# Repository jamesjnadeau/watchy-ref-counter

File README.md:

Intial prompt:

Based on the firmware available here: 

https://github.com/sqfmi/Watchy

I have clone the repo locally at ../Watchy

I'm creating a purpose built countdown timer used for reffing a football game. 

The user should see a countdown on the screen that updates every second. 
The count down should have 2 configurable start timers, start with 40 and 25 as defaults.
The user should use the two buttons on the right hand side of the device to start the timers. The top one should be the longer value
The timer buttons should have a configurable hold down before it acts as a reset of the timer, or to start the timer in general. Make it be 0.5 seconds as a default.

When the timer is up, it should buzz a configurable time, start with 1 second. 
Before the timer reaches a configurable number of seconds, default with 10 seconds, it should buzz a configurable number of times, start with 1. By default it should buzz once at 10 seconds. 

It should count down the last 5 seconds by buzzing at each second mark. So it should buzz at 5, 4, 3, 2, and 1, then do the finall configuable buzz time.
The top left button, after being held down for a configurable ammount of time, different than the above one, default 1 second, should then put the device into low power mode. The device should wake back up to normal operating mode if this button is pressed again, If in lower power mode, it should say sleeping on the display.

Please create a read me seciton below the line that documents the structure of the repo and how to install it on the device.

---

# Watchy Ref Counter

A countdown timer for sports officials, running on a
[Watchy](https://watchy.sqfmi.com) e-paper watch. Seven presets — football,
lacrosse, NCAA and NFHS baseball, NCAA and NFHS softball, and a custom slot —
each with two countdowns, big 7-segment digits, and a buzz pattern you can
follow without looking at your wrist.

**This repo stands alone.** It does not link against the
[Watchy library](https://github.com/sqfmi/Watchy); the panel is driven through
GxEPD2, the RTC chips directly over I2C, NTP through the ESP32 core's own SNTP
client, and the Bluetooth time sync through its BLE stack. Where the behaviour follows that firmware — the menu, the
set-time screen, the pin map — the comments credit it, but none of its code is
here. It builds with the reference repo nowhere on disk.

## Controls

Watchy's four buttons, by physical position:

```
   BACK (top left)  ----+---------+---- UP   (top right)
                        |  200 x  |
   MENU (bottom left) --|  200    |---- DOWN (bottom right)
                        +---------+
```

Watch out for the names: on Watchy, **MENU is the bottom-left button and BACK
is the top-left one**, which is the opposite of what they sound like.

| Button | Action | Default hold |
| --- | --- | --- |
| Top right | Start, or reset, the active preset's **long** clock | 0.5s |
| Bottom right | Start, or reset, the active preset's **short** clock | 0.5s |
| Top left | Enter low power mode; hold again to wake | 1.0s |
| Bottom left | On Ready, open the settings menu; otherwise clear the clock | 0.5s |

The two right-hand buttons always run whichever preset is active — see
*Sports* below — rather than a fixed 40 and 25 seconds.

The bottom-left button does two jobs because on the Ready screen there is no
clock to clear. Hold it there and you get the reference Watchy menu; hold it
while a clock is up and it clears back to Ready.

**A short tap does nothing.** Every action needs a deliberate hold, so a button
brushed against a sleeve mid-game cannot reset the play clock. A short
confirmation buzz fires the instant a hold registers, so you know the clock
started without looking down.

Holding a timer button while that clock is already running restarts it from
its full value.

## Sports

The right-hand buttons run whichever preset is active. Seven ship in the box
— six fixed sports plus one editable Custom slot:

| Name | Description |
| --- | --- |
| Football | football |
| Lacrosse | lacrosse shot |
| Base NCAA | NCAA baseball |
| Base NFHS | NFHS baseball |
| Soft NCAA | NCAA softball |
| Soft NFHS | NFHS softball |
| Custom | user set |

Their clock lengths and buzz marks are in *Buzz pattern*, below. `Football`
reproduces exactly what this firmware shipped with before presets existed, so
a watch that has never opened the menu behaves the same as it always did.

The active choice comes from the menu's `Sport` row, which opens a scrolling
picker: UP/DOWN moves, MENU selects and persists, BACK leaves the stored
choice alone. Like the time zone, it is kept in NVS, so it survives a
reflash — the sport a watch is set to is a property of who is carrying it,
not of the firmware on it.

Each row shows a preset's name and its two clock values; the footer below
shows the highlighted preset's description, its position in the list, and its
two warning marks as `warn <first>/<second>`. The final-countdown value isn't
there — it's 5 for every fixed preset, so it never tells two of them apart,
and it's shown spelled out on the Custom editor instead, the one preset that
can change it.

The six fixed presets are read-only. `Edit Custom` opens the one preset that
can be changed: five fields — Long, Short, Warn 1, Warn 2, Final — with
MENU stepping to the next field and committing once past the last one, BACK
stepping back, and UP/DOWN changing the value under the cursor, the same
interaction Set Time uses. The two clocks clamp to 1–199 seconds; the three
marks clamp to 0–199, where 0 turns that mark off. Editing Custom does not
select it — pick `Custom` from the `Sport` screen to make it active, the same
separation the zone picker keeps between "known" and "in use".

## Buzz pattern

Every preset buzzes on the same four events, at the marks that preset sets:

| Event | Buzz |
| --- | --- |
| First warning, at `warnAtSeconds` remaining | `WARNING_BUZZ_COUNT` (1) short buzz |
| Second warning, at `warn2AtSeconds` remaining | `WARNING_BUZZ_COUNT_2` (2) short buzzes |
| Final countdown, at or below `finalCountdownFrom` | 1 short buzz (150ms) on each second mark |
| Expire, at 0 | 1 long buzz (1000ms) |

A mark of 0 turns it off — Football's second warning ships off, which is why
the stock clock only ever buzzes once early. A mark that falls at or inside
the final countdown is silently swallowed by the per-second buzz, which
already covers it. The two buzz counts and the expire length are global, in
`settings.h`; the marks themselves are per-preset, in `RefSport.cpp`:

| Name | Long | Short | Warn 1 | Warn 2 | Final from |
| --- | --- | --- | --- | --- | --- |
| Football | 40 | 25 | 10 | – | 5 |
| Lacrosse | 120 | 20 | 30 | 10 | 5 |
| Base NCAA | 120 | 20 | 30 | 10 | 5 |
| Base NFHS | 80 | 20 | 30 | 10 | 5 |
| Soft NCAA | 90 | 20 | 30 | 10 | 5 |
| Soft NFHS | 60 | 20 | 20 | 10 | 5 |
| Custom | 40 | 25 | 10 | – | 5 |

Every mark above is in seconds **remaining**, matching what the clock counts
down. This is worth being deliberate about, because
[ReadyRef](https://ready-ref.com/personal-timers/) — the commercial timers
this preset table is modelled on — quote their pre-warnings in seconds
*elapsed*. Their football timer's "30 second pre-warning" on a 40 second
clock is the same moment as Football's `Warn 1` of 10 above: 30 seconds in is
10 seconds left. Getting that backwards would fire the warning at the wrong
end of the play.

Buzzes are deliberately blocking, and fire *before* the screen redraws: the
buzz is the cue you actually react to, and an e-paper refresh takes most of a
second. This costs no accuracy, because remaining time is always recomputed
from the timestamp the clock started at rather than accumulated tick by tick.

## Screens

Every screen carries the wall clock at the top left and a battery gauge at the
top right.

**Ready** — shown at boot and on wake. Both of the active preset's clocks
stacked to line up with the two right-hand buttons that start them. The
footer shows the active sport's name, in capitals, in place of `HOLD TO
START` — the thing worth checking before kickoff is which preset is loaded,
not how the buttons work.

**Running** — the current clock, large, updating every second. The header is
the same wall clock and battery gauge every screen carries; it does not say
which of the two clocks is counting.

**Time expired** — `00` holds for `EXPIRED_HOLD_MS` (3s), long enough to
register the delay of game, then the watch drops back to Ready on its own.
Starting a new clock during that window cancels the return.

**Sleeping** — low power mode.

**Menu** — held open from Ready. Navigation follows the reference: UP/DOWN to
move, MENU (bottom left) to select, BACK (top left) to leave. It also drops
back to Ready by itself after `MENU_TIMEOUT_MS`, so a menu opened by accident
cannot strand you mid-game. Nine entries do not fit the panel at once, so the
list scrolls a seven-row window, keeping the highlighted entry in view the same
way the time zone picker already does. Two of the nine are conditional — **Sync
NTP** and **Sync BT** — and with neither on offer the remaining seven fit
without scrolling at all.

Every screen the menu opens times out on the same rule, and a timeout always
**discards**: Set Time leaves the clock alone, Edit Custom leaves the stored
preset alone, and the two pickers leave their stored choice alone. Only
pressing MENU past the last field commits. This matters more than it sounds —
these screens repaint about twice a second, so one left open would otherwise
hold the panel refreshing until the battery went flat.

| Entry | What it does |
| --- | --- |
| About | Version, board name, battery, time, uptime, last sync, RTC type |
| Sync NTP | Connect and set the clock from `NTP_SERVER`. Only listed once **Setup WiFi** has connected |
| Sync BT | Set the clock from a phone over Bluetooth. Listed whenever `BT_TIME_SYNC` is on |
| TZ: *name* | Pick a US time zone from a scrolling list |
| DST: Auto/Off | Turn the daylight saving rule on or off |
| Set Time | Set the clock by hand, no WiFi needed |
| Setup WiFi | Captive portal to save credentials |
| Sport: *name* | Pick one of the seven presets from a scrolling list |
| Edit Custom | Set the five Custom fields by hand |

The **Sport**, **TZ** and **DST** rows show their current value rather than
fixed text, so the menu doubles as the status display for all three. **DST**
toggles in place and redraws with a fast partial refresh; everything else
opens a screen.

**Sync NTP** is hidden until **Setup WiFi** has connected successfully, since
with no credentials stored it could only ever report a failure. The watch
remembers that in NVS (`RefWifi.cpp`), so it survives a reflash — but a watch
upgraded from a firmware without that flag has nothing stored and will hide the
row until **Setup WiFi** is run once more. A setup that fails or times out
clears the flag again, correctly: that screen wipes the saved credentials
before it raises its access point.

**Sync BT** is the other way round: it needs nothing saved, so it is there from
the first boot. It advertises the watch for `BT_SYNC_TIMEOUT_MS` (60s) and
waits for a phone to write the time; the screen says when a phone has
connected, BACK gives up early, and the result screen names the zone the
conversion used. See *Setting the clock from a phone* below for what to press
on the phone.

There is no "Show Accelerometer". The reference has one, but nothing on a play
clock reads the sensor, and leaving it out means the BMA423 is never powered
up at all. There is no "Vibrate Motor" buzz test either — the buzzer announces
every warning mark and every expiry, so a dedicated screen for it earned a menu
row it did not need.

## Time zones and daylight saving

The RTC holds UTC. The zone offset is applied on the way out, every time the
clock is read, which is what makes the two menu entries cheap: changing zone or
flipping the DST switch takes effect on the next redraw and never rewrites the
clock chip.

The **TZ** entry lists all eleven US zones by name, with their standard offset
on the row and the abbreviations and region underneath:

| Zone | Standard | Daylight | Where |
| --- | --- | --- | --- |
| Eastern | UTC−5 EST | EDT | NY, DC, Atlanta, Miami |
| Central | UTC−6 CST | CDT | Chicago, Dallas, Minneapolis |
| Mountain | UTC−7 MST | MDT | Denver, Salt Lake, Albuquerque |
| Arizona | UTC−7 MST | — | most of Arizona |
| Pacific | UTC−8 PST | PDT | LA, Seattle, SF, Las Vegas |
| Alaska | UTC−9 AKST | AKDT | most of Alaska |
| Aleutian | UTC−10 HST | HDT | western Aleutians |
| Hawaii | UTC−10 HST | — | Hawaii |
| Samoa | UTC−11 SST | — | American Samoa |
| Atlantic | UTC−4 AST | — | Puerto Rico, USVI |
| Chamorro | UTC+10 ChST | — | Guam, N. Marianas |

**DST: Auto** means the US federal rule is applied when the date calls for it —
forward at 02:00 local standard on the second Sunday in March, back at 02:00
local daylight on the first Sunday in November — not that the clock is shifted
year round. Nothing needs doing at a changeover: the offset is computed from
the instant being displayed, so the watch is right on both sides of it and
right again if it is rebooted or asleep across it. **DST: Off** pins the zone
to standard time all year. The five zones with no daylight saving ignore the
switch either way.

Both settings are stored in NVS, so they survive a reflash — the zone is a
property of where the watch is, not of the firmware on it. `DEFAULT_TIME_ZONE`
and `DEFAULT_DST_AUTO` in `settings.h` are only the starting point, used until
the menu has been used once.

The rule is the one in force since 2007 (Energy Policy Act of 2005). It is
verified against the real transition dates for 2024–2027 and 2030 in every
zone; see *Testing* below. Set Time is exact except for the one hour a year
that springing forward deletes — typing 02:30 on that morning stores 01:30,
because 02:30 never happens.

## Timekeeping

The time comes from the watch's RTC chip, which `RefRtc` probes for at boot —
a PCF8563 at 0x51 on the V2.0, an RV-3028-C7 at 0x52 on the C6 board. It
keeps running through low power mode and
through a reflash, so the watch only needs setting once. The About screen
reports which one was found.

The chip is kept in UTC, not local time. That is what lets the zone and DST
settings change with no clock write and no drift, and it means an NTP sync
needs no offset applied to it.

Drift is handled three ways. **Set Time** sets it by hand, in local time.
**Sync BT** sets it from a phone over Bluetooth, with no WiFi involved.
**Sync NTP** sets it from the internet, on demand from the menu. It also runs
itself automatically once WiFi credentials have been saved, on a schedule
that needs both of these to be true: the watch has sat untouched — no button
press, no sleep entry — for `NTP_RESYNC_HOURS` (3 by default), and at least
`NTP_MIN_SYNC_INTERVAL_HOURS` (24) have passed since the last attempt, so a
run of idle moments in a row cannot trigger back-to-back radio activity.
Sleep entry counts as activity in its own right, so putting the watch away
resets the quiet clock rather than letting it tick through the night. Set
`NTP_RESYNC_HOURS` to 0 to only ever sync by hand. A PCF8563 drifts roughly a
minute a month, so even a daily sync keeps that under a second. The C6 board's
RV-3028-C7 is factory trimmed to about half a minute a year, and needs the
sync far less.

The two chips do not share a register layout, and the difference is the kind
that fails quietly: the PCF8563 holds the date at 0x05 and the weekday at
0x06, while the RV-3028 has the weekday at 0x03 and the date at 0x04. Decoding
one with the other's map yields a day of the month between 0 and 6 — wrong,
but shaped like a date. `tests/rtc_test.cpp` pins both layouts against a stub
I2C bus, which is the only part of this that can be checked without hardware.

An automatic sync blocks for several seconds while the radio comes up, which
is why it waits for quiet rather than firing the moment nobody is looking.
That holds even in low power mode: the watch arms a deep-sleep timer against
the same schedule, wakes itself when a sync falls due, syncs, and goes
straight back to sleep — the SLEEPING screen already on the panel is never
touched. It never runs while a clock is counting.

### Setting the clock from a phone

**Sync BT** is for the case WiFi does not cover: a field with no network you
have credentials for, and a phone in your pocket that knows the time.

The watch is the peripheral. While the screen is open it advertises the
standard Bluetooth **Current Time Service** (`0x1805`) under `BT_DEVICE_NAME`,
and the phone connects and *writes* the time into it. That direction is the
only one that works without an app written for this watch: neither iOS nor
Android will hand its clock to an arbitrary peripheral that asks for it, but
writing into a watch's Current Time Service is exactly what the service is
for. It is the same route the open source PineTime firmware takes, which is
why the apps that already do it work here unchanged:

| On the phone | What to do |
| --- | --- |
| **Gadgetbridge** (Android, F-Droid) | Pair the watch as a generic device; it syncs time to a connected device on its own |
| **nRF Connect** (Android / iOS) | Connect, open service `0x1805`, write characteristic `0x2A2B` |
| Anything else that syncs time to a BLE watch | Point it at the Current Time Service |

Two characteristics are accepted, both standard:

| UUID | What it carries |
| --- | --- |
| `0x2A2B` Current Time | year, month, day, hour, minute, second — the clock itself |
| `0x2A0F` Local Time Information | the UTC offset that clock is expressed in |

The first is the one that matters. The second decides how the wall clock a
phone writes becomes the UTC the RTC holds: with it, the phone's own offset is
used and the watch's **TZ** setting does not enter into it; without it, the
time is taken as local to whatever zone the watch is set to, exactly as a time
typed into **Set Time** would be. Most clients send only the first, which is
fine as long as the phone and the watch agree about the zone — and the result
screen says which of the two happened, so an hour out is diagnosable rather
than mysterious. A write is refused outright if it does not parse or falls
outside a sane range, so a stray or malformed packet cannot set the clock to
1970.

Nothing is bonded or encrypted. The only thing a stranger in radio range can
do is set the watch's clock, and only in the minute the screen is open; that
is not worth pairing every phone that might want to set it. The radio is up
only inside that window — `RefBleTime::begin()` starts the controller and
`end()` takes it back down — so a watch that never opens the screen pays
nothing for the feature but the flash it occupies.

Automatic sync stays with NTP by default. Set `BT_AUTO_SYNC_SECONDS` above 0
and a due sync that NTP could not satisfy — no credentials, or a failed
connection — falls back to advertising for that long, which is worth having
only if a companion app on a phone syncs time to this watch by itself. The two
radios are never up at once: WiFi is dropped before Bluetooth starts.

The header clock is repainted on its own partial window when the minute rolls
over, so keeping it live costs one ~400ms refresh a minute rather than a whole
screen. It is deliberately **not** updated while a clock is counting down: the
tick path stays reserved for the countdown, so the time can sit stale for as
long as the active clock runs — up to 199s on Custom at its ceiling — and
catches up as soon as the clock stops.

## Repo structure

```
watchy-ref-counter/
├── README.md          this file
├── platformio.ini     build config; one env per supported board (V2.0, C6)
└── RefCounter/        the sketch (also a valid Arduino IDE sketch folder)
    ├── RefCounter.ino main loop and the IDLE/RUNNING/EXPIRED/SLEEPING states
    ├── settings.h     every tunable number, and nothing else
    ├── board.h        the pin map, per revision, and button polarity
    ├── Buttons.h/.cpp debounced reads with one-shot hold detection
    ├── Buzzer.h/.cpp  vibration motor
    ├── RefPanel.h/.cpp    the GxEPD2 panel instance and its pins
    ├── RefDisplay.h/.cpp  screen layout and e-paper refresh strategy
    ├── RefRtc.h/.cpp      the PCF8563 and RV-3028-C7 clocks, over I2C
    ├── RefClock.h/.cpp    timekeeping, NTP sync, battery
    ├── RefZone.h/.cpp     US time zones and the daylight saving rule
    ├── RefSegments.h/.cpp  where the countdown digits land, host-tested
    ├── RefSport.h/.cpp     sport presets and the custom slot
    ├── RefWifi.h/.cpp      whether WiFi has ever been set up, host-tested
    ├── RefMenuItems.h/.cpp the menu's row order and labels, host-tested
    └── RefMenu.h/.cpp      the settings menu
```

### Dependencies

Three libraries, all from the registry:

| Library | For |
| --- | --- |
| GxEPD2 | the GDEY0154D67 panel, including fast partial update |
| Adafruit GFX | fonts and primitives |
| WiFiManager | the captive portal behind "Setup WiFi" |

Bluetooth adds no fourth: the BLE stack and its GATT server come with the
ESP32 Arduino core, and the Current Time Service is a handful of bytes this
project encodes itself, in `RefCtsTime.cpp`.

Everything else is either this project's own or comes with the ESP32 Arduino
core. Notably there is **no RTC library**: each RTC is a handful of BCD
registers, and talking to them directly avoids a dependency that caused
trouble — one whose `master` no longer compiles against a current core.

The folder is named `RefCounter/` so it satisfies the Arduino IDE's rule that a
sketch folder match its `.ino`, while `platformio.ini` points `src_dir` at the
same folder. One copy of the source, two build systems.

### Design notes

**Why none of the Watchy library is used.** Its `Watchy::init()` is the whole
lifecycle — wake, draw one frame, deep sleep — and it ends in `deepSleep()`
without returning, which cannot work for a clock that ticks every second. That
alone forced an own main loop. Reusing just the menu then proved impossible
too: `Watchy::showMenu()` hard-codes six entries, and `showBuzz()`, `setTime()`
and `showSyncNTP()` each finish by redrawing it, so "Show Accelerometer" could
not be dropped without it flashing back for 2.6s after most actions. With the
menu written here anyway, the remaining pieces — a GxEPD2 wrapper, two RTC
chips and an NTP call — were smaller than the dependency they justified.

**Digits are drawn, not typed.** The countdown is seven filled rectangles per
digit rather than a font glyph. That keeps the countdown's exact bounding box
knowable, which is what lets the partial-update window below be hard-coded
safely — the claim now rests on `layoutCount` in `RefSegments.cpp`, which is
host-tested against its own 199 ceiling, rather than on the countdown always
being exactly two digits — and it drops the 14KB DSEG7 font from the build.
The segment geometry is four numbers (`SegStyle`) per size, instantiated in
`RefDisplay.cpp`, so resizing the digits is a one-line change.

**Refresh strategy.** Three tiers, cheapest first:

| Call | Area | Cost | Used for |
| --- | --- | --- | --- |
| `renderDigits()` | 200x124 window | ~280ms | every second of a running clock |
| `render(v, false)` | whole screen, partial | ~400ms | state changes (start, expire, wake) |
| `render(v, true)` | whole screen, full | ~2.6s | returning to Ready |

`renderDigits()` repaints only the countdown into the framebuffer and calls
GxEPD2's `displayWindow()`, so only 62% of the panel is driven — the header,
footer and battery are left standing. The window widened from 176px to the
full 200px so it always covers the skinny hundreds bar; the extra cost every
second is the price of never leaving a stale leading `1` behind when a clock
crosses back under 100.

Partial refreshes leave faint ghosting, and only a full refresh clears it. Both
routes back to Ready arrange for one, but neither pays for it up front:

- **A clock expires.** `00` holds for three seconds, then the return to Ready
  is itself the full refresh. One redraw does both jobs, and by then play has
  stopped.
- **You clear it by hand.** The return is a *partial* refresh, so the button
  responds in ~400ms rather than freezing for 2.6s. The full refresh is queued
  for `SCREEN_TIDY_DELAY_MS` later and only fires once nothing is happening;
  starting a clock cancels it.

Either way the 2.6s stall never lands mid-down.

**Power.** The CPU drops to 80MHz, and the watch light-sleeps between button
polls whenever no clock is running, waking on a button GPIO with a 250ms timer
as a backstop. Low power mode is a real deep sleep with an `ext1` wake on the
top-left button, plus a timer wake armed against the NTP resync schedule so
the watch can correct its clock unattended. Set `LIGHT_SLEEP_WHEN_IDLE` to
`false` in `settings.h` to fall back to plain polling if your board misbehaves.

**Accuracy.** The countdown is derived from `esp_timer_get_time()` against the
main crystal. Light sleep during e-paper busy-waits is accounted for using the
calibrated RTC slow clock, which drifts a fraction of a percent — on the order
of a tenth of a second across a 40 second count.

## Configuring

Everything lives in [`RefCounter/settings.h`](RefCounter/settings.h). The ones
you are most likely to touch:

```c
static const char     DEFAULT_SPORT[]      = "Football"; // until set in the menu
static const uint16_t CUSTOM_LONG_SECONDS  = 40;  // the Custom slot's factory
static const uint16_t CUSTOM_SHORT_SECONDS = 25;  //   values, likewise only a
static const uint16_t CUSTOM_WARN_SECONDS  = 10;  //   starting point
static const uint16_t CUSTOM_WARN2_SECONDS = 0;   // 0 = off
static const uint16_t CUSTOM_FINAL_FROM    = 5;
static const uint32_t TIMER_HOLD_MS        = 500;  // hold to start / reset
static const uint32_t SLEEP_HOLD_MS        = 1000; // hold for low power mode
static const uint32_t BUZZ_EXPIRE_MS       = 1000; // buzz at zero
static const uint8_t  WARNING_BUZZ_COUNT   = 1;    // buzzes at the first mark
static const uint8_t  WARNING_BUZZ_COUNT_2 = 2;    // buzzes at the second
static const bool     DARK_MODE           = true;  // true = white on black
static const bool     CLOCK_24_HOUR       = false;
static const char     DEFAULT_TIME_ZONE[] = "Eastern"; // until set in the menu
static const bool     DEFAULT_DST_AUTO    = true; // apply the US rule by date
static const uint32_t NTP_RESYNC_HOURS    = 3;  // 0 = only sync by hand
static const uint32_t NTP_MIN_SYNC_INTERVAL_HOURS = 24; // floor since last try
static const bool     BT_TIME_SYNC        = true; // false drops the Sync BT row
static const char     BT_DEVICE_NAME[]    = "Ref Counter"; // as seen by phones
static const uint32_t BT_SYNC_TIMEOUT_MS  = 60000; // how long it waits
static const uint32_t BT_AUTO_SYNC_SECONDS = 0; // 0 = manual Bluetooth only
```

`DEFAULT_SPORT` and the five `CUSTOM_*` values are likewise only a starting
point. The clock lengths themselves moved to the on-watch menu — `Sport` picks
among the six fixed presets, and `Edit Custom` changes the Custom slot's
numbers on the watch, with both choices kept in NVS across a reflash. Editing
these constants and reflashing only changes what a watch starts on before
anyone has touched its menu.

`DEFAULT_TIME_ZONE` and `DEFAULT_DST_AUTO` are only defaults — the menu's
**TZ** and **DST** entries override them and the choice is kept in NVS across
reflashes.

`DARK_MODE` flips the whole theme, panel border included. The stock Watchy
`7_SEG` face ships with its own `DARKMODE true`, which is why it is white on
black; there is no inversion in the display driver itself.

Clock values are limited to 1–199. The display draws two full-size digits
plus, for 100 and up, a skinny leading `1` — just the two vertical bars of a
`1`, one segment thick — to their left; the two full digits shift right to
make room. There is no room for a fourth glyph, which is why 199 is the
ceiling.

The timing values are no longer reflash-only: they sit behind the on-watch
`Sport` and `Edit Custom` entries, which need a deliberate hold from the Ready
screen to reach and time out on their own if left open, the same protection
against a fumbled button that the rest of the menu has. The six fixed presets
cannot be edited at all — only the Custom slot can, and only from the watch.

If the buttons on your unit sit in different positions than the diagram above,
swap the four role defines at the bottom of
[`RefCounter/board.h`](RefCounter/board.h) rather than editing the sketch.

## Installing

This firmware supports two boards: the **Watchy V2.0** (ESP32) and **this
repo's own ESP32-C6-MINI-1 design** in [`board-files/`](board-files/). V1.0,
V1.5 and V3 were dropped — the V1 revisions put the up button and the battery
tap on other pins, V1.0 carries a different RTC chip entirely, and V3's ESP32-S3
target has been superseded by the C6 board. `board.h` stops the build if any of
their revision flags is set, rather than flashing a pin map built for other
hardware.

### Option A — PlatformIO (recommended)

Requires [PlatformIO Core](https://platformio.org/install/cli) or the VS Code
extension.

Nothing to check out first — the three libraries are pulled from the registry
on the first build. Plug the watch in, then build and flash. Pick the env for
your board — `watchy_v2` (the default) or `watchy_c6`:

```bash
pio run -e watchy_v2 -t upload
```

`watchy_c6` pulls a different PlatformIO platform — the pioarduino fork —
because the official `espressif32` tops out at Arduino-ESP32 2.0.17, which has
no ESP32-C6 support at all. Note that the board has never been fabricated and
its RV-3028-C7 has no driver in this firmware yet, so a C6 build cannot keep
time across a power cut.

The first build downloads about 1.5GB of ESP32 toolchain and takes a few
minutes; later builds take under a minute.

### Option B — Arduino IDE

1. **Board support.** In *Preferences → Additional Board Manager URLs* add:
   `https://raw.githubusercontent.com/espressif/arduino-esp32/gh-pages/package_esp32_index.json`
   then install **esp32** (2.0.5 or newer) from *Tools → Board → Boards Manager*.

2. **Libraries.** *Tools → Manage Libraries*, then install **GxEPD2**,
   **Adafruit GFX Library** and **WiFiManager** (tzapu). Accept the dependency
   prompts. Do *not* install the Watchy library; this sketch does not use it.

3. **Board target.** *Tools → Board → ESP32 Arduino* → **ESP32 Dev Module**
   for the V2.0. The pin map is this project's own, so the board only has to
   be the right chip. (The C6 board is PlatformIO-only here; the IDE's ESP32-C6
   support depends on a 3.x core that this project does not otherwise require.)

   Then set the revision. The IDE has no build-flag field, so uncomment this
   line near the top of [`RefCounter/board.h`](RefCounter/board.h) — it has to
   go in that header, which every source file includes, not in the `.ino`,
   which would only set it for itself:

   ```c
   // #define ARDUINO_WATCHY_V20
   ```

   Under PlatformIO this is handled by `build_flags` and no edit is needed.

   Also set *Tools → Partition Scheme* to **Huge APP**, or the WiFi and
   Bluetooth stacks will not fit.

4. **Open and upload.** Open `RefCounter/RefCounter.ino`, select the serial
   port under *Tools → Port*, and hit Upload.

### If upload fails

The watch must be awake to enumerate over USB. If it is in low power mode, hold
the top-left button to wake it first.

On the **C6 board**, there is no button to hold: the download-boot strapping
pin is IO9, and this board deliberately puts no button on it, so a stuck or
dirty button can never drop the watch into the bootloader by accident.
Forcing download mode means shorting the **TP1** test pad to ground at
reset. The V2.0 has no button on GPIO 0 and relies on the USB serial chip's
auto-reset instead, so there is no button to hold there either; if
auto-reset is not working, it is a cable or port problem rather than a
timing one.

## Testing

`RefZone.cpp`, `RefSegments.cpp`, `RefSport.cpp`, `RefWifi.cpp`,
`RefCtsTime.cpp` and `RefMenuItems.cpp` carry no panel, no GPIO and no radio,
so they compile on a host and the daylight saving rule, the digit layout, the
preset table, the WiFi flag, the Bluetooth time payloads and the menu's row
order are all checked off the watch — this is exactly the kind of bug (a
changeover date, a digit running off the panel, a clamp, a menu row in the
wrong place, a Bluetooth packet believed when it should not be) that is
expensive to find on hardware and cheap to catch here.

```bash
./tests/run.sh
```

`tests/tz_test.cpp` walks the exact transition instants for 2024, 2025, 2026,
2027 and 2030, checks January and July in all eleven zones, checks that
**DST: Off** pins every zone to standard time, and round-trips 1,460 local
times through local → UTC → local. `tests/tz_edges.cpp` prints what Set Time
does inside the two transition hours. Both build the shipped `RefZone.cpp`
against a stub `Preferences` that reports nothing stored, so the `settings.h`
defaults apply.

`tests/segments_test.cpp` pins `layoutCount`'s numbers for the two styles the
panel actually uses — the two-digit and three-digit layouts, the exact pixel
`x` positions, the 100/99 boundary where the hundreds bar appears and
disappears, and clamping above 199 — then checks, exhaustively and for both
the big (RUNNING/EXPIRED) and small (Ready) styles, that no digit runs off
either edge of the panel for every value 0 through 199. SMALL is not a
theoretical case: the Ready screen draws both of the active preset's clocks
in it, and Lacrosse, Base NCAA and Custom all reach past 100. It checks
`layoutRows` the same way, including the invariant that the upper, middle
and lower segment rows abut with no gap or overlap.

`tests/sport_test.cpp` checks the shipped preset table against the numbers in
*Buzz pattern* above, that `Custom` is always the last entry, that an out-of-range index
falls back to the first preset rather than reading off the end of the table,
and that every name and description fits the menu row and picker footer they
render into. It also exercises persistence itself: the stub `Preferences`
gained a switch (`PreferencesStub::enable`) so a test can turn storage on,
which the time zone tests deliberately never do. With it on, `sport_test`
confirms the selected sport and the edited Custom fields both survive a
simulated reboot (a fresh `RefSport::begin()` call), and that a garbage index
left in NVS clamps back to the first preset rather than being trusted.

`tests/wifi_test.cpp` checks that a watch with nothing stored — or with NVS
unavailable — reads as never set up, and that the flag survives a simulated
reboot in both directions.

`tests/cts_time_test.cpp` covers the Bluetooth Current Time payloads: the ten
byte layout a phone writes, every field's range, the month lengths and the
leap year rule, the year window that throws out a phone whose own clock has
never been set, the short writes that are still understood and the ones that
are not, that a rejected write leaves the caller's `struct tm` untouched, and
that a wrong day-of-week in the packet is recomputed rather than trusted. It
does the same for Local Time Information — negative zones, half hour zones,
the "unknown" values — and round-trips what the watch publishes back through
its own parser, since a phone reading the watch and a phone writing to it must
agree about the same offset.

`tests/menu_items_test.cpp` pins the menu's row order for all four
combinations of its two conditional rows, that **Sync NTP** is absent until
WiFi is set up and **Sync BT** is present from the first boot, and that
**Setup WiFi** shifts from slot 4 to slot 6 as they appear above it — which is
the case the menu's redraw depends on, since running **Setup WiFi** inserts a
row above the one the user is standing on. It also checks that every label fits
the 18 glyphs the panel has room for, and that the removed buzz test has not
crept back in.

Nothing else here has automated tests, and none of this has run on hardware —
see below.

`tests/board_test.cpp` and `tests/board_c6_test.cpp` add a second kind of
check: they assert the V2.0 and C6 pin maps and each board's `BOARD_NAME`,
which until now nothing did for the C6 at all. `tests/run.sh` then compiles
`board.h` three more times, once per retired revision flag, to confirm each is
rejected rather than quietly building the V2.0 map.

`tests/rtc_test.cpp` runs the real `RefRtc` against a stub I2C bus
(`tests/stub/Wire.h`), where a device is a flat file of registers. It covers
both chips' BCD decoding, both register layouts, the two "the time is not set"
flags — the PCF8563's low-voltage bit and the RV-3028's power-on reset bit —
and a write-then-read round trip. Mutating the RV-3028 reader to use the
PCF8563's date register, or to skip the power-on reset check, fails it.

## Known limitations

- **None of this has been run on a watch.** It builds clean for both supported
  boards and the time zone, digit-layout and sport-preset logic are tested
  on a host, but no part of it has been exercised on real hardware. The least
  proven pieces are `RefPanel::begin()` (GxEPD2's stock init rather than the
  reference firmware's tuned one), light sleep, and whether the four buttons
  are physically where `board.h` says they are. `RefRtc`'s BCD decoding and
  chip probing used to head that list; they are now covered by
  `tests/rtc_test.cpp` against a stub bus, which proves the arithmetic but
  not that either chip answers on a real board.
- Sport presets add their own untested territory: whether the leading `1`
  actually clears from the panel when a clock crosses 100 → 99 (the widened
  refresh window is the fix; only a real panel confirms it), whether nine
  menu rows scroll legibly with the highlight landing on the right row, and
  whether the Custom editor's five rows fit without the descenders clipping.
  NVS is assumed to survive a reflash for the `refsport` namespace the way it
  reportedly does for `refzone`, but that has never been confirmed either.
- Longer presets mean longer runs of partial refreshes: a 40s Football clock
  was already 39 consecutive `displayWindow` ticks before the deferred full
  refresh, but a 120s Lacrosse clock is 119 and Custom at its 199 ceiling is
  198. The full refresh on the way back to Ready still runs and still clears
  it, so nothing is broken, but how much ghosting a run that long leaves on a
  real panel in between is untested like everything else here.
- Buttons are not sampled during a buzz or a screen refresh. A hold that starts
  and ends inside one of those windows is missed; a hold you keep held is
  always caught, up to ~400ms late.
- Continuous running is the worst case for battery. Expect several hours of
  active use on a full charge; use low power mode between games.
- Bringing up WiFi for an NTP sync blocks for several seconds, and buttons are
  ignored for that whole time. It only happens after 60s untouched, and never
  during a countdown, but it is a real pause if you catch it.
- Only US time zones are listed. Elsewhere, pick whichever standard offset
  matches and turn **DST** off, or add a row to the table in `RefZone.cpp`.
- The daylight saving rule is the current US one, hard-coded. If Congress makes
  daylight saving permanent, this needs a firmware change.
- Adding WiFi grew the binary from 402KB to 1.13MB and RAM use from 29KB to
  55KB. Both are comfortably within a 4MB / 320KB device. Bluetooth adds the
  BLE stack on top of that; the `huge_app` partition leaves room for it, but
  the exact figure has not been measured here — see below.
- **The Bluetooth sync has not been run against a phone.** The byte layouts
  are host-tested and the GATT calls are written to the API that every
  Arduino-ESP32 backend shares, but nothing has confirmed that a real phone
  finds the watch, writes to it and lands on the right minute. Nor has the
  build itself been compiled: the toolchain could not be fetched in the
  environment this was written in, so the firmware figures above are the
  pre-Bluetooth ones.
- A phone will not volunteer its clock. **Sync BT** needs an app on the phone
  that writes the Current Time Service — Gadgetbridge does it by itself, nRF
  Connect does it by hand — and there is no route that works from a stock
  phone with nothing installed.
- Nothing is bonded or encrypted, so anyone in radio range can set the clock
  while the **Sync BT** screen is open. That window is a minute long and the
  worst outcome is a wrong time, which is why it is left open.
- A phone that sends no zone with the time is assumed to be in the zone the
  watch is set to. Travel to a different zone with **TZ** left behind and the
  clock lands an hour or more out; the result screen says which assumption it
  made.

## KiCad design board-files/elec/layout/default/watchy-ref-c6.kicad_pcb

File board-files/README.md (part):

# Watchy Ref — ESP32-C6-MINI-1 / RV-3028-C7 board

A Watchy-compatible watch board carrying an ESP32-C6-MINI-1 module and an
RV-3028-C7 real-time clock, with the accelerometer, the USB-serial bridge and
the UART console deleted and USB-C in place of micro-USB. Derived from
[sqfmi/watchy-hardware](https://github.com/sqfmi/watchy-hardware) `v2.0`
(MIT), which supplies the e-paper, charging, power and motor circuitry
unchanged.

Design rationale, with the reasoning behind every decision:
[`docs/superpowers/specs/2026-08-18-c6-mini-rv3028-board.md`](../docs/superpowers/specs/2026-08-18-c6-mini-rv3028-board.md).

> **Never fabricated, never powered, never tested.** Read
> [`UNVERIFIED.md`](UNVERIFIED.md) before doing anything with these files.

## The design is code

The electrical design is not a drawn schematic. It is
[atopile](https://atopile.io) source under `elec/src/`, compiled to a KiCad
netlist. Reading `elec/src/watchy.ato` top to bottom tells you what is
connected to what, and `git diff` on it says exactly what a change did —
which is not true of a `.kicad_sch`.

The tradeoff is real and worth stating: there is no schematic sheet to print
and hand to someone. `ato view` draws a block diagram, but it is not a
schematic. If you want one, KiCad's netlist import gives you a rat's nest, not
a drawing.

```
board-files/
  ato.yaml                          project and build config
  requirements.txt                  the compiler version, pinned exactly
  elec/src/watchy.ato               the board: every part and every connection
  elec/src/parts.ato                passives, discretes, connectors, switches
  elec/src/mcu.ato                  ESP32-C6-MINI-1
  elec/src/rtc.ato                  RV-3028-C7
  elec/src/usb.ato                  USB-C receptacle and the ESD array
  elec/footprints/footprints.pretty custom footprints
  elec/layout/default/              the PCB (see "Layout" below)
  checks/netlist_check.py           design assertions against the netlist
  checks/drc_check.py               runs KiCad's DRC and judges the result
  checks/make_bom.py                fab BOM generator
  checks/run.sh                     build, assert, generate, check the board
  elec/layout/v2-baseline.kicad_pcb V2's layout, untouched; the overlap reference
  scripts/apply_netlist.py          netlist -> PCB, headless (mutates the board)
  scripts/route.py                  routes the board, headless (mutates it too)
  scripts/check_board.py            asserts the PCB matches the netlist
  fab/BOM.csv                       generated, committed
  vendor/                           upstream licence notices
```

## Building and checking it

```bash
python3 -m venv ~/.venvs/ato
~/.venvs/ato/bin/pip install -r requirements.txt
ATO=~/.venvs/ato/bin/ato ./checks/run.sh
```

That compiles the sources to `build/default.net`, runs the assertions, writes
`fab/BOM.csv`, checks the board against the netlist and runs DRC. Expect
`0 problem(s)` and 54 placements.

**Install from `requirements.txt`, not `pip install atopile`.** The pin is
`atopile==0.2.67` and it is exact on purpose: the floating install now gets
0.12.6, which refuses to run at all ("the CLI has been replaced by the app at
app.atopile.io"). `checks/run.sh` checks the version and stops if it is
wrong. `requirements.txt` records what every newer release does — the short
version is that 0.3 through 0.11 reject these sources, 0.12 is dead, 0.14 and
0.15 need Python 3.14, and 0.16+ is a hosted application rather than a CLI.
There is no upgrade that keeps this a headless build.

The assertions encode the constraints the spec cares about and that no
compiler can see:

| Check | What it catches |
| --- | --- |
| pin map | any GPIO that drifted from the spec's table |
| deep-sleep wake pins | a button or `RTC_INT` on a pin above IO21, which cannot wake `ext1` |
| battery ADC on ADC1 | the battery tap landing on ADC2, which is dead while WiFi is on |
| strapping pins | anything but the `TP_BOOT` test pad touching IO9 |
| USB-C CC pulldowns | a missing or shared 5.1k, and D+/D- halves left untied |
| RV-3028-C7 wiring | `VDD` off `+BATT`, or `VBACKUP` fed from a rail |
| bus pull-ups | I2C or `RTC_INT` pulled to `+BATT`, putting 4.2V on C6 inputs |
| buttons active low | a switch still wired to `+3V3`, or a leftover pull-down |
| battery divider | the divider back at 100k, or missing its filter cap |
| MCU power | the `-N4R2` variant, a floating module ground pad, EN misrouted |
| V2 blocks carried over | any drift across the 106 pads of the 43 parts transcribed from V2 |
| deleted parts | the PICO-D4, CP2102, BMA423, PCF8563, crystal or antenna creeping back |

And on the board (`scripts/check_board.py`):

| Check | What it catches |
| --- | --- |
| components | a netlist part with no footprint, or a footprint the netlist does not name |
| nets | any pad on the wrong net, or on a net where the netlist says nothing |
| mechanical | the four switches, the FPC and the battery connector drifting off V2's coordinates |
| stackup | the board falling back to 2 layers, or a missing GND / +3V3 plane |
| outline | Edge.Cuts not closing, or a cutout reappearing inside the board |
| pads on board | any pad off the edge — this is how the USB-C was found facing the wrong way |
| antenna | the module's keepout allowing pour, or not overhanging the board edge |

And DRC itself (`checks/drc_check.py`), which runs `kicad-cli pcb drc` and
holds the result to a policy rather than to a count: zero unconnected items,
zero errors except an allowlist that names each accepted violation and says
why. It also reports allowlist entries that no longer occur, so the list
cannot quietly rot.

All of these were mutation-tested: the netlist or the board was deliberately
broken in the way each check describes, and the check caught it. A check that
cannot fail is not a check.

**What is not checked: ERC — and it cannot be.** `kicad-cli sch erc` reads a
`.kicad_sch`, and this project has none; the design is atopile source
compiled straight to a netlist. Nothing looks for driven-output conflicts or
unconnected pins beyond what the assertions above happen to cover. That is a
standing cost of defining the design in code, not a temporary gap. See
[`UNVERIFIED.md`](UNVERIFIED.md).

## Layout

`elec/layout/default/watchy-ref-c6.kicad_pcb` started as V2's board, converted
from KiCad 5 and switched to a 4-layer stackup. Two scripts turn it into this
design, in order, and both are re-runnable:

```bash
python3 scripts/apply_netlist.py --dry-run   # report only
python3 scripts/apply_netlist.py             # placement, nets, planes, outline
python3 scripts/route.py                     # copper
python3 scripts/check_board.py               # verify, independently
```

They need the interpreter KiCad's `pcbnew` bindings were built against — the
system `python3`, not a venv.

### apply_netlist.py — everything except the copper

KiCad's "Import Netlist" is a GUI dialog and `kicad-cli` has no equivalent, so
this does the job with `pcbnew`. It removes the interior cutouts from
Edge.Cuts and the rule areas V2 no longer needs, deletes the parts the netlist
dropped, replaces the ones whose footprint changed *while preserving V2's
position* (most of those swaps are only a KiCad 5→7 library rename, and losing
placement over a rename would defeat the point of pinning the designators),
adds the new parts, assigns all 249 pads to their 73 nets, and lays the GND,
`+3V3` and `VBUS` pour outlines.

It also strips V2's branding — the `watchy` and `SQFMI` lettering on the mask
layers, and the two sqfmi logo footprints. This is a derivative reference
design and should not be fabricated carrying another project's marks; the
attribution belongs in this file, not etched into the board. It happens to be
worth 119 DRC errors as well: mask lettering is drawn as *apertures*, so the
word is bare copper, and every via, track and pad passing beneath one bridged
to it. The display outline (`REF**` on B.Fab) is kept — it comes from the same
library and carries the name, but it is a mechanical outline rather than a
mark, and it is what stops anything being placed under the panel.

Placement comes from a table in the script, and that table is authoritative —
it is re-applied on every run, to parts already on the board as well as to new
ones. The board is generated from these sources, so a position that only
exists because somebody dragged it in the GUI is a position nothing records.
Move a part by editing the table; the script reports every courtyard overlap
the table produces, and the fix is to edit the table again.

### route.py — the copper

There is no autorouter in KiCad and no routing API, so this is a maze router
written against `pcbnew`. It deletes every existing track and via first —
V2's routing was still on the board, and routed for V2's netlist it shorted
nets rather than connecting them — then:

- drops a via into each of the module's thermal pads. It has to: the array is
  1.2mm pads on a 1.65mm pitch, and the 0.45mm gaps are too narrow for a pour
  to enter and too narrow for a via to sit beside. Espressif's reference
  layout does the same.
- ties every pad on a poured net to its pour through its own via, except
  where the pour already touches the pad. Which nets are poured, and which of
  their pads the pour reaches, are read off the board rather than listed in
  the router -- so the two scripts cannot drift apart, and a pour that covers
  only part of its net leaves the rest as ordinary routing work.
- routes the signal nets with A* on F.Cu and B.Cu over a 0.1mm grid, hardest
  first: the differential pair and the charge-pump loop before anything can
  cross them, then whichever nets have the least room to escape their pads.
- rips up and re-routes. A net that cannot get through has usually lost a lane
  to one that went first, so a second search finds which nets are in the way,
  deletes their copper, puts the stuck net through the gap and re-routes them
  somewhere else. This is what takes the board from "almost" to finished.
- stitches GND between F.Cu, In1.Cu and B.Cu on a 3mm grid, last, in whatever
  room the signals left.
- fills the zones and reports what is still unconnected.

Power is mostly not routed as copper. GND and `+3V3` are whole-board planes
on In1.Cu and In2.Cu and a pad reaches them through a via, which is what buys
the space to route everything else on two layers.

`VBUS` is a third pour, and a bounded one. It carries the charge current -- in
at the USB-C, out through the Schottky to VSYS and into the TP4054 -- so it
wants copper rather than a track, and as eleven thin tracks fighting for lanes
it was the net the router most often failed to place. It sits on In2.Cu at a
higher priority than `+3V3`, over the block that actually carries the current:
`J2`'s four VBUS pads, `U3.5`, `C11.2`, `R14.1`, `Q4.1` and `U5.4`.

It is sized to that block and not to the net. A hull around all eleven VBUS
pads is a 202mm2 diagonal band that reaches clear across the board to collect
`D4` and `D5`, and swallows `U2.5` -- the LDO 3V3 output -- on the way, which
would strand it. Bounded to the block it costs 82mm2, traps nothing, and
leaves `D4` and `D5` as two ordinary tracks, which is what they are: stubs
hanging off the block.

In2.Cu rather than B.Cu, which is where an earlier note here suggested putting
it. Both work, but In2.Cu is already a power layer so the pour costs no
routing space, whereas the same shape on B.Cu would sit straight on top of the
`J2`/`U3`/`U5`/`Q4` congestion -- the most contested copper on the board. The
cost is a split in the `+3V3` plane under one corner of B.Cu, a return-path
discontinuity for anything crossing it, which at SPI and 12Mbps USB is not a
real concern. `VBUS_POUR_LAYER` in `apply_netlist.py` moves it.

The pour is not free. The nine covered pads are all on F.Cu, so each needs a
through via to reach In2.Cu, and a through via blocks all four layers -- nine
of them land in the tightest part of the board. `VBUS` itself routes now, and
one fewer net fails overall, but those vias took lanes `USB_DM` and `VSYS` had
been using. It is the right shape for the current path either way; it is not
the thing that finishes the board.

Every via the router places is tented on both sides. Half of them sit in a pad
field or inside a thermal pad, where a bare mask aperture would bridge to the
neighbouring pad and wick solder off the joint.

#### The board is the only source of truth

The router keeps an occupancy grid to search over, and the grid has to agree
with the copper. It used not to. There were three stores of truth rather than
two: the board, the grid, and `owned` -- a side table of which items belong to
which net -- and the grid was rebuilt from `owned`, never from the board. Any
copper that fell out of that table, or was added without updating it, was
still physically on the board and completely invisible to the router.

That is not a hypothetical. It is where `SCL` came to cross `EPD_DC` and
`EPD_BUSY` on B.Cu: a failed attempt left a partial path behind, `owned` was
overwritten with the retry, and every later rebuild pretended the old copper
was not there. Eight shorts, and nothing in the router could have noticed.

So `rebuild()` now stamps from `board.GetTracks()` and the grid is a pure
function of the board. `owned` survives as an index -- it is how a net's items
are found when it is ripped up -- but nothing is derived from it. A net can
drop out of it and the grid stays correct.

That needed one snapshot split into two, because they were doing different
jobs under one name:

| | |
| --- | --- |
| `blank` | the board with **no** copper: outline, keepouts, pads, holes. `rebuild()` and `audit()` start here, so a recomputation owes nothing to the router's own record of itself |
| `immovable` | `blank` plus the power copper. What the rip-up scout treats as *hard*: a cell blocked here is a pad or a plane drop and cannot move, while one blocked only in the live grid is some signal's track and can be ripped |

Handing the scout `blank` would let it plan routes straight through power it
may not touch, which is the bug you get for free by moving the snapshot
without noticing it had two roles.

Searching still stamps incrementally -- rebuilding after every track would be
far too slow -- so correctness rests on the incremental path matching a fresh
one. `audit()` proves it: recompute from the board, compare cell by cell,
report any difference with its coordinates and both values. This is sound
because stamping is monotone: a cell goes free -> one net -> contested and
never back, so re-stamping the same items always lands in the same state
whatever order they arrive in. A fresh rebuild is therefore the ground truth
an incrementally-updated grid must equal.

It runs every pass and prints under "GRID DISAGREED WITH THE BOARD". Anything
it reports is a bug in `route.py`; no board can legitimately make the grid and
the copper disagree. It is mutation-tested in both directions -- copper added
to the board without telling the grid, and copper removed from it -- and
catches each with the cell coordinates and both values.

#### What it does not finish

The router does not get everything. It routes the power, every ground pad and
41 of the 44 signal nets; **three are left unrouted** — `EPD_SCK` at `U1.28`,
`PREVGH` at `J1.21` and `USB_DM` at `J2.A7` — for 3 unconnected items on the
board. `route.py` exits non-zero, and `drc_check.py` and `checks/run.sh` fail,
until they are cleared. That is deliberate: a board that is 93% routed should
not be able to look finished.

`route.py` also exits non-zero on a stranded ground pad — one the pours never
reached and no via was dropped into — because a floating return is a defect
and not a cosmetic complaint. There are none at present, but they are the
failure this board produces when the right-hand side gets crowded, and they
were invisible until the pour slivers hiding them were deleted.

Which nets and which pads move between runs — the router is not deterministic
across attempts, because each attempt feeds the previous one's failures back
in. The counts are stable; the names are not.

What the router does lay down is clean. On the current board it produces **no
shorts, no crossing tracks and no clearance violations of its own**, and DRC
reports **zero errors that are not on `drc_check.py`'s accepted list** — every
clearance and hole-clearance error left is internal to a footprint (`Q4`/`R15`
at 0.165mm, inherited from V2; `J2`'s own mounting holes against its own
pads). Getting there took four fixes, each found by DRC rather than by design,
and they are worth knowing before trusting the next change:

| Bug | Symptom |
| --- | --- |
| overlapping clearance halos resolved last-writer-wins | a cell claimed by two nets became one net's, and that net then routed through the other's clearance. 96 clearance errors |
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
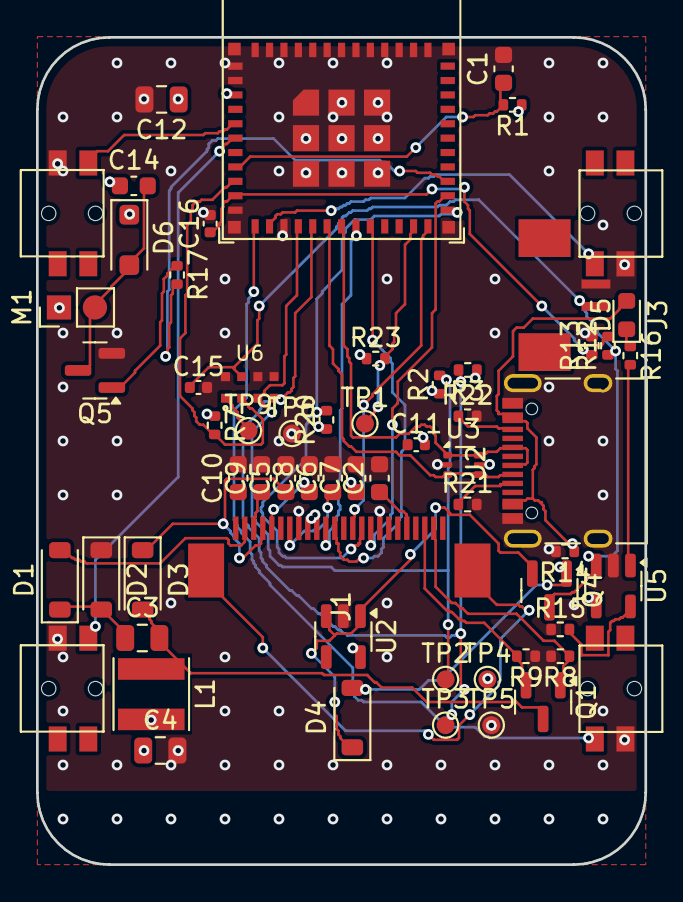
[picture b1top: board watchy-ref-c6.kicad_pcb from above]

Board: 4 copper layers, 33.8 x 46.0 mm, 61 parts (0 on the bottom side), 43 nets.

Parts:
C1, C14: 100nF; C_0603_1608Metric
C2, C5, C6, C7, C8, C9, C10: 1uF/50V; C_0603_1608Metric
C3, C4, C12: 4.7uF/50V; C_0805_2012Metric
C11: 4.7uF; C_0402_1005Metric
C15, C16: 100nF; C_0402_1005Metric
D1, D2, D3, D4: MBR0530 Schottky; D_SOD-123
D5: LED (charge status); LED_0603_1608Metric
D6: 1N4001; D_SOD-123F
J1: FPC24 0.5mm ZIF; 24_Pins_0.5mm_Pitch_ZIF_Connector_UP
J2: USB-C 2.0 receptacle, 16 pin; USB_C_Receptacle_XKB_U262-16XN-4BVC11
J3: JST 1.25mm battery connector; 1.25T-2PWT (Molex 532610271)
L1: 10uH 1A; L_Taiyo-Yuden_NR-40xx
M1: Vibration motor pads; Motor_Header
Q1: AO3400A N-channel MOSFET; SOT-23
Q4: CJ2301 P-channel MOSFET; SOT-23
Q5: S8050 NPN; SOT-23
R1, R7, R8, R14, R15, R23: 10k; R_0402_1005Metric
R2, R3: 4.7k; R_0402_1005Metric
R9: 3R; R_0402_1005Metric
R12, R13: 1M; R_0402_1005Metric
R16, R17: 1k; R_0402_1005Metric
R20: 100k; R_0402_1005Metric
R21, R22: 5.1k; R_0402_1005Metric
SW1, SW2, SW3, SW4: Side tactile switch; K2-1114SA-A4SW-06
TP1: GPIO0; TestPoint_Pad_D1.0mm
TP2: SCL; TestPoint_Pad_D1.0mm
TP3: SDA; TestPoint_Pad_D1.0mm
TP4: 3V3; TestPoint_Pad_D1.0mm
TP5, TP6: GND; TestPoint_Pad_D1.0mm
TP9: 1.0mm test pad; TestPoint_Pad_D1.0mm
U1: ESP32-C6-MINI-1
U2: ME6211C33M5G-N 3.3V LDO; SOT-23-5
U3: USBLC6-2P6 USB ESD array; SOT-666
U5: TP4054 Li-ion charger; SOT-23-5
U6: RV-3028-C7 RTC; RV-3028-C7

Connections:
+3V3: C4.1, C7.1, C12.1, C14.1, D6.1, J1.15, J1.16, L1.2, M1.1, R1.1, R2.1, R3.1, R7.1, R20.1, R23.1, TP4.1, U1.3, U2.5
+BATT: C15.1, J3.1, Q4.3, R12.1, U5.3, U6.7
BATT_ADC: C16.1, R12.2, R13.1, U1.10
BTN_BACK: SW2.2, U1.13
BTN_DOWN: SW4.2, U1.6
BTN_MENU: SW1.2, U1.12
BTN_UP: SW3.2, U1.5
CC1: J2.A5, R21.1
CC2: J2.B5, R22.1
CHRG: R16.2, U5.1
CP_NEG: C3.1, D1.1, D2.2
CP_POS: C3.2, D3.2, L1.1, Q1.3
EN: C1.1, R1.2, U1.8
EPD_BUSY: J1.9, U1.26
EPD_C5: C2.1, J1.5
EPD_C18: C6.1, J1.18
EPD_C20: C8.1, J1.20
EPD_C22: C9.1, J1.22
EPD_C24: C10.1, J1.24
EPD_CS: J1.12, U1.22
EPD_DC: J1.11, U1.24
EPD_MOSI: J1.14, U1.19
EPD_RST: J1.10, R20.2, U1.25
EPD_SCK: J1.13, U1.20
GDR: J1.2, Q1.1, R8.1
GND: C1.2, C2.2, C4.2, C5.2, C6.2, C7.2, C8.2, C9.2, C10.2, C11.1, C12.2, C15.2, C16.2, D2.1, J1.8, J1.17, J2.A1, J2.A12, J2.B1, J2.B12, J2.S1, J3.2, Q5.2, R8.2, R9.1, R13.2, R14.2, R15.1, R21.2, R22.2, SW1.1, SW2.1, SW3.1, SW4.1, TP5.1, TP6.1, U1.1, U1.2, U1.11, U1.14, U1.36, U1.37, U1.38, U1.39, U1.40, U1.41, U1.42, U1.43, U1.44, U1.45, U1.46, U1.47, U1.48, U1.49, U1.50, U1.51, U1.52, U1.53, U2.2, U3.2, U5.2, U6.5, U6.6, U6.8
LED_A: D5.1, R16.1
MOTOR_DRV: C14.2, D6.2, M1.2, Q5.3
PREVGH: C5.1, D3.1, J1.21
PREVGL: D1.2, J1.23
PROG: R15.2, U5.5
RESE: J1.3, Q1.2, R9.2
RTC_CLKOUT: TP9.1, U6.1
RTC_INT: R7.2, U1.9, U6.2
SCL: R2.2, TP2.1, U1.15, U6.3
SDA: R3.2, TP3.1, U1.16, U6.4
TP_BOOT: R23.2, TP1.1, U1.23
USB_DM: J2.A7, J2.B7, U1.17, U3.3, U3.4
USB_DP: J2.A6, J2.B6, U1.18, U3.1, U3.6
VBUS: C11.2, D4.2, D5.2, J2.A4, J2.A9, J2.B4, J2.B9, Q4.1, R14.1, U3.5, U5.4
VIB_BASE: Q5.1, R17.1
VIB_PWM: R17.2, U1.27
VSYS: D4.1, Q4.2, U2.1, U2.3

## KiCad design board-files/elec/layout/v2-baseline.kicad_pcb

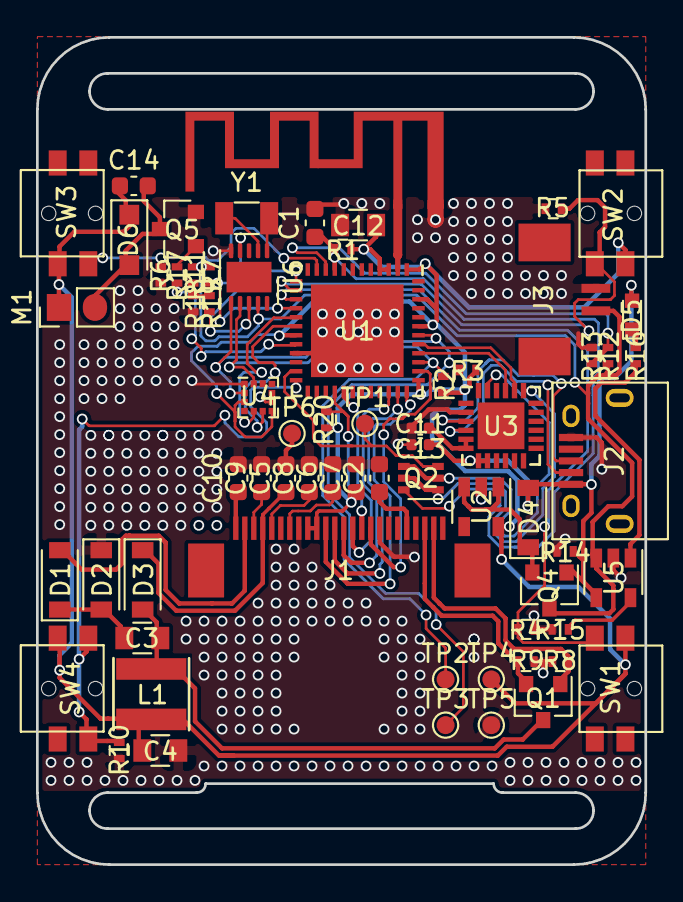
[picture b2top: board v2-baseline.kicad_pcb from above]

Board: 4 copper layers, 33.8 x 46.0 mm, 67 parts (0 on the bottom side), 52 nets.

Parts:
AE1: SWRA117D
C1, C14: 100nF; C_0603_1608Metric
C2, C5, C6, C7, C8, C9, C10: 1uF/50V; C_0603_1608Metric
C3, C4, C12: 4.7uF/50V; C_0805
C11, C13: 4.7uF; C_0402_1005Metric
D1, D2, D3, D4: MBR0530; D_SOD-123
D5: LED; LED_0603
D6: 1N4001; D_SOD-123F
J1: FPC24(0.5MM); 24_Pins_0.5mm_Pitch_ZIF_Connector_UP
J2: Micro USB; USB_Micro-B
J3: Battery; 1.25T-2PWT (Molex 532610271)
L1: 10uH 1A; Inductor_Taiyo-Yuden_NR-40xx
M1: Vibration_Motor; Motor_Header
Q1: AO3400A; SOT-23
Q2: UMH3N; SOT-363_SC-70-6
Q4: CJ2301; SOT-23
Q5: S8050; SOT-23
R1, R4, R5, R6, R7, R8, R10, R14, R15: 10K; R_0402
R2, R3: 4.7K; R_0402
R9: 3; R_0402
R11: 680K; R_0402
R12, R13, R19, R20: 100K; R_0402
R16, R17: 1K; R_0402
R18: 220K; R_0402
SW1, SW2, SW3, SW4: BTN; K2-1114SA-A4SW-06
TP1: GPIO0; TestPoint_Pad_D1.0mm
TP2: SCL; TestPoint_Pad_D1.0mm
TP3: SDA; TestPoint_Pad_D1.0mm
TP4: 3V3; TestPoint_Pad_D1.0mm
TP5, TP6: GND; TestPoint_Pad_D1.0mm
U1: ESP32-PICO-D4; QFN-48-1EP_7x7mm_Pitch0.5mm
U2: ME6211C33M5G-N; SOT-23-5
U3: CP2102; QFN-24-1EP_4x4mm_Pitch0.5mm
U4: BMA423; LGA-12_2x2mm_Pitch0.5mm
U5: TP4054; SOT-23-5
U6: PCF8563BS; DFN-10-1EP_3x3mm_P0.5mm_EP1.7x2.5mm
Y1: 32.768KHz; Crystal_SMD_3215-2Pin_3.2x1.5mm

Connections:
32KHZ: R19.2, U1.13, U6.8
+3V3: C4.1, C7.1, C12.1, C14.1, D6.1, J1.15, J1.16, L1.2, M1.1, R1.1, R2.1, R3.1, R20.1, SW1.1, SW2.1, SW3.1, SW4.1, TP4.1, U1.1, U1.3, U1.4, U1.19, U1.37, U1.43, U1.46, U2.5, U4.3, U4.7
+BATT: J3.1, Q4.3, R7.1, R11.1, R12.1, U5.3, U6.9
ACC_INT_1: U1.17, U4.5
ACC_INT_2: U1.18, U4.6
ADC: R12.2, R13.1, U1.10
BTN_1: R4.2, SW1.2, U1.15
BTN_2: R5.2, SW2.2, U1.14
BTN_3: R6.2, SW3.2, U1.11
BTN_4: R10.2, SW4.2, U1.24
BUSY: J1.9, U1.38
DC: J1.11, U1.29
DTR: Q2.2, Q2.4, U3.23
EN: C1.1, Q2.6, R1.2, U1.9
GDR: J1.2, Q1.1, R8.1
GND: AE1.2, C1.2, C2.2, C4.2, C5.2, C6.2, C7.2, C8.2, C9.2, C10.2, C11.1, C12.2, C13.2, D2.1, J1.8, J1.17, J2.5, J3.2, Q5.2, R4.1, R5.1, R6.1, R8.2, R9.1, R10.1, R13.2, R14.2, R15.1, R18.2, TP5.1, TP6.1, U1.21, U1.49, U2.2, U3.2, U4.1, U4.8, U4.9, U5.2, U6.5
GPIO0: Q2.3, TP1.1, U1.23
MOSI: J1.14, U1.36
unnamed: AE1.1, U1.2
unnamed: C2.1, J1.5
unnamed: C3.1, D1.1, D2.2
unnamed: C3.2, D3.2, L1.1, Q1.3
unnamed: C6.1, J1.18
unnamed: C8.1, J1.20
unnamed: C9.1, J1.22
unnamed: C10.1, J1.24
unnamed: C13.1, U3.5, U3.6
unnamed: C14.2, D6.2, M1.2, Q5.3
unnamed: D4.1, Q4.2, U2.1, U2.3
unnamed: D5.1, R16.1
unnamed: J2.2, U3.4
unnamed: J2.3, U3.3
unnamed: Q5.1, R17.1
unnamed: R11.2, R18.1, R19.1
unnamed: R15.2, U5.5
unnamed: R16.2, U5.1
unnamed: U6.1, Y1.1
unnamed: U6.2, Y1.2
PREVGH: C5.1, D3.1, J1.21
PREVGL: D1.2, J1.23
RES: J1.10, R20.2, U1.28
RESE: J1.3, Q1.2, R9.2
RTC_INT: R7.2, U1.16, U6.4
RTS: Q2.1, Q2.5, U3.19
RX: U1.40, U3.21
SCK: J1.13, U1.35
SCL: R2.2, TP2.1, U1.39, U4.12, U6.7
SDA: R3.2, TP3.1, U1.42, U4.2, U6.6
SS: J1.12, U1.34
TX: U1.41, U3.20
VBUS: C11.2, D4.2, D5.2, J2.1, Q4.1, R14.1, U3.7, U3.8, U5.4
VIB_PWM: R17.2, U1.20

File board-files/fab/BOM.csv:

Quantity,Value,Footprint,Library,Designators
1,JST 1.25mm battery connector,1.25T-2PWT (Molex 532610271),footprints,J3
1,FPC24 0.5mm ZIF,24_Pins_0.5mm_Pitch_ZIF_Connector_UP,footprints,J1
2,100nF,C_0402_1005Metric,Capacitor_SMD,"C15,C16"
1,4.7uF,C_0402_1005Metric,Capacitor_SMD,C11
2,100nF,C_0603_1608Metric,Capacitor_SMD,"C1,C14"
7,1uF/50V,C_0603_1608Metric,Capacitor_SMD,"C2,C5,C6,C7,C8,C9,C10"
3,4.7uF/50V,C_0805_2012Metric,Capacitor_SMD,"C3,C4,C12"
4,MBR0530 Schottky,D_SOD-123,Diode_SMD,"D1,D2,D3,D4"
1,1N4001,D_SOD-123F,Diode_SMD,D6
1,ESP32-S3-MINI-1,ESP32-S3-MINI-1,footprints,U1
4,Side tactile switch,K2-1114SA-A4SW-06,footprints,"SW1,SW2,SW3,SW4"
1,LED (charge status),LED_0603_1608Metric,LED_SMD,D5
1,10uH 1A,L_Taiyo-Yuden_NR-40xx,Inductor_SMD,L1
1,Vibration motor pads,Motor_Header,footprints,M1
1,RV-3028-C7 RTC,RV-3028-C7,footprints,U6
1,100k,R_0402_1005Metric,Resistor_SMD,R20
6,10k,R_0402_1005Metric,Resistor_SMD,"R1,R7,R8,R14,R15,R23"
2,1M,R_0402_1005Metric,Resistor_SMD,"R12,R13"
2,1k,R_0402_1005Metric,Resistor_SMD,"R16,R17"
1,3R,R_0402_1005Metric,Resistor_SMD,R9
2,4.7k,R_0402_1005Metric,Resistor_SMD,"R2,R3"
2,5.1k,R_0402_1005Metric,Resistor_SMD,"R21,R22"
1,AO3400A N-channel MOSFET,SOT-23,Package_TO_SOT_SMD,Q1
1,CJ2301 P-channel MOSFET,SOT-23,Package_TO_SOT_SMD,Q4
1,S8050 NPN,SOT-23,Package_TO_SOT_SMD,Q5
1,ME6211C33M5G-N 3.3V LDO,SOT-23-5,Package_TO_SOT_SMD,U2
1,TP4054 Li-ion charger,SOT-23-5,Package_TO_SOT_SMD,U5
1,USBLC6-2P6 USB ESD array,SOT-666,Package_TO_SOT_SMD,U3
1,"USB-C 2.0 receptacle, 16 pin",USB_C_Receptacle_XKB_U262-16XN-4BVC11,Connector_USB,J2

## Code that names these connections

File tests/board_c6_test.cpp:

// The C6 board's pin map, asserted. Every number here comes from
// board-files/elec/src/watchy.ato by way of board.h; board.h's own comment
// notes that the netlist half is checked by board-files/checks and this half
// was checked by nothing. Now it is checked by this.

#define ARDUINO_ESP32C6_DEV // as platformio.ini's watchy_c6 env does

#include <stdio.h>

#include "board.h"

static_assert(PIN_I2C_SDA == 7 && PIN_I2C_SCL == 6, "C6 I2C pins");
static_assert(PIN_SPI_SCK == 15 && PIN_SPI_MISO == 23 && PIN_SPI_MOSI == 14 &&
                  PIN_SPI_SS == 8,
              "C6 SPI pins; MISO is a spare, the panel is write-only");
static_assert(PIN_BTN_MENU == 0 && PIN_BTN_BACK == 1 && PIN_BTN_UP == 2 &&
                  PIN_BTN_DOWN == 3,
              "C6 buttons are IO0-IO3, all LP GPIOs so one ext1 mask covers "
              "them");
static_assert(PIN_DISPLAY_CS == 8 && PIN_DISPLAY_DC == 18 &&
                  PIN_DISPLAY_RST == 19 && PIN_DISPLAY_BUSY == 20,
              "C6 panel control pins");
static_assert(PIN_VIB_MOTOR == 21, "C6 vibration motor");
static_assert(PIN_BATT_ADC == 5, "C6 battery tap");
static_assert(BTN_PRESSED_LEVEL == LOW,
              "C6 buttons pull their pin low when pressed");

int main() {
  printf("board: C6 pin map ok\n");
  return 0;
}

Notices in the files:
board-files/README.md:
Licences:
- The V2 design this is derived from: MIT, `vendor/LICENSE-watchy-hardware.txt`.
- The ESP32-C6-MINI-1 footprint: CC-BY-SA 4.0 from
[espressif/kicad-libraries](https://github.com/espressif/kicad-libraries),
`vendor/LICENSE-espressif-kicad-libraries.md`.
